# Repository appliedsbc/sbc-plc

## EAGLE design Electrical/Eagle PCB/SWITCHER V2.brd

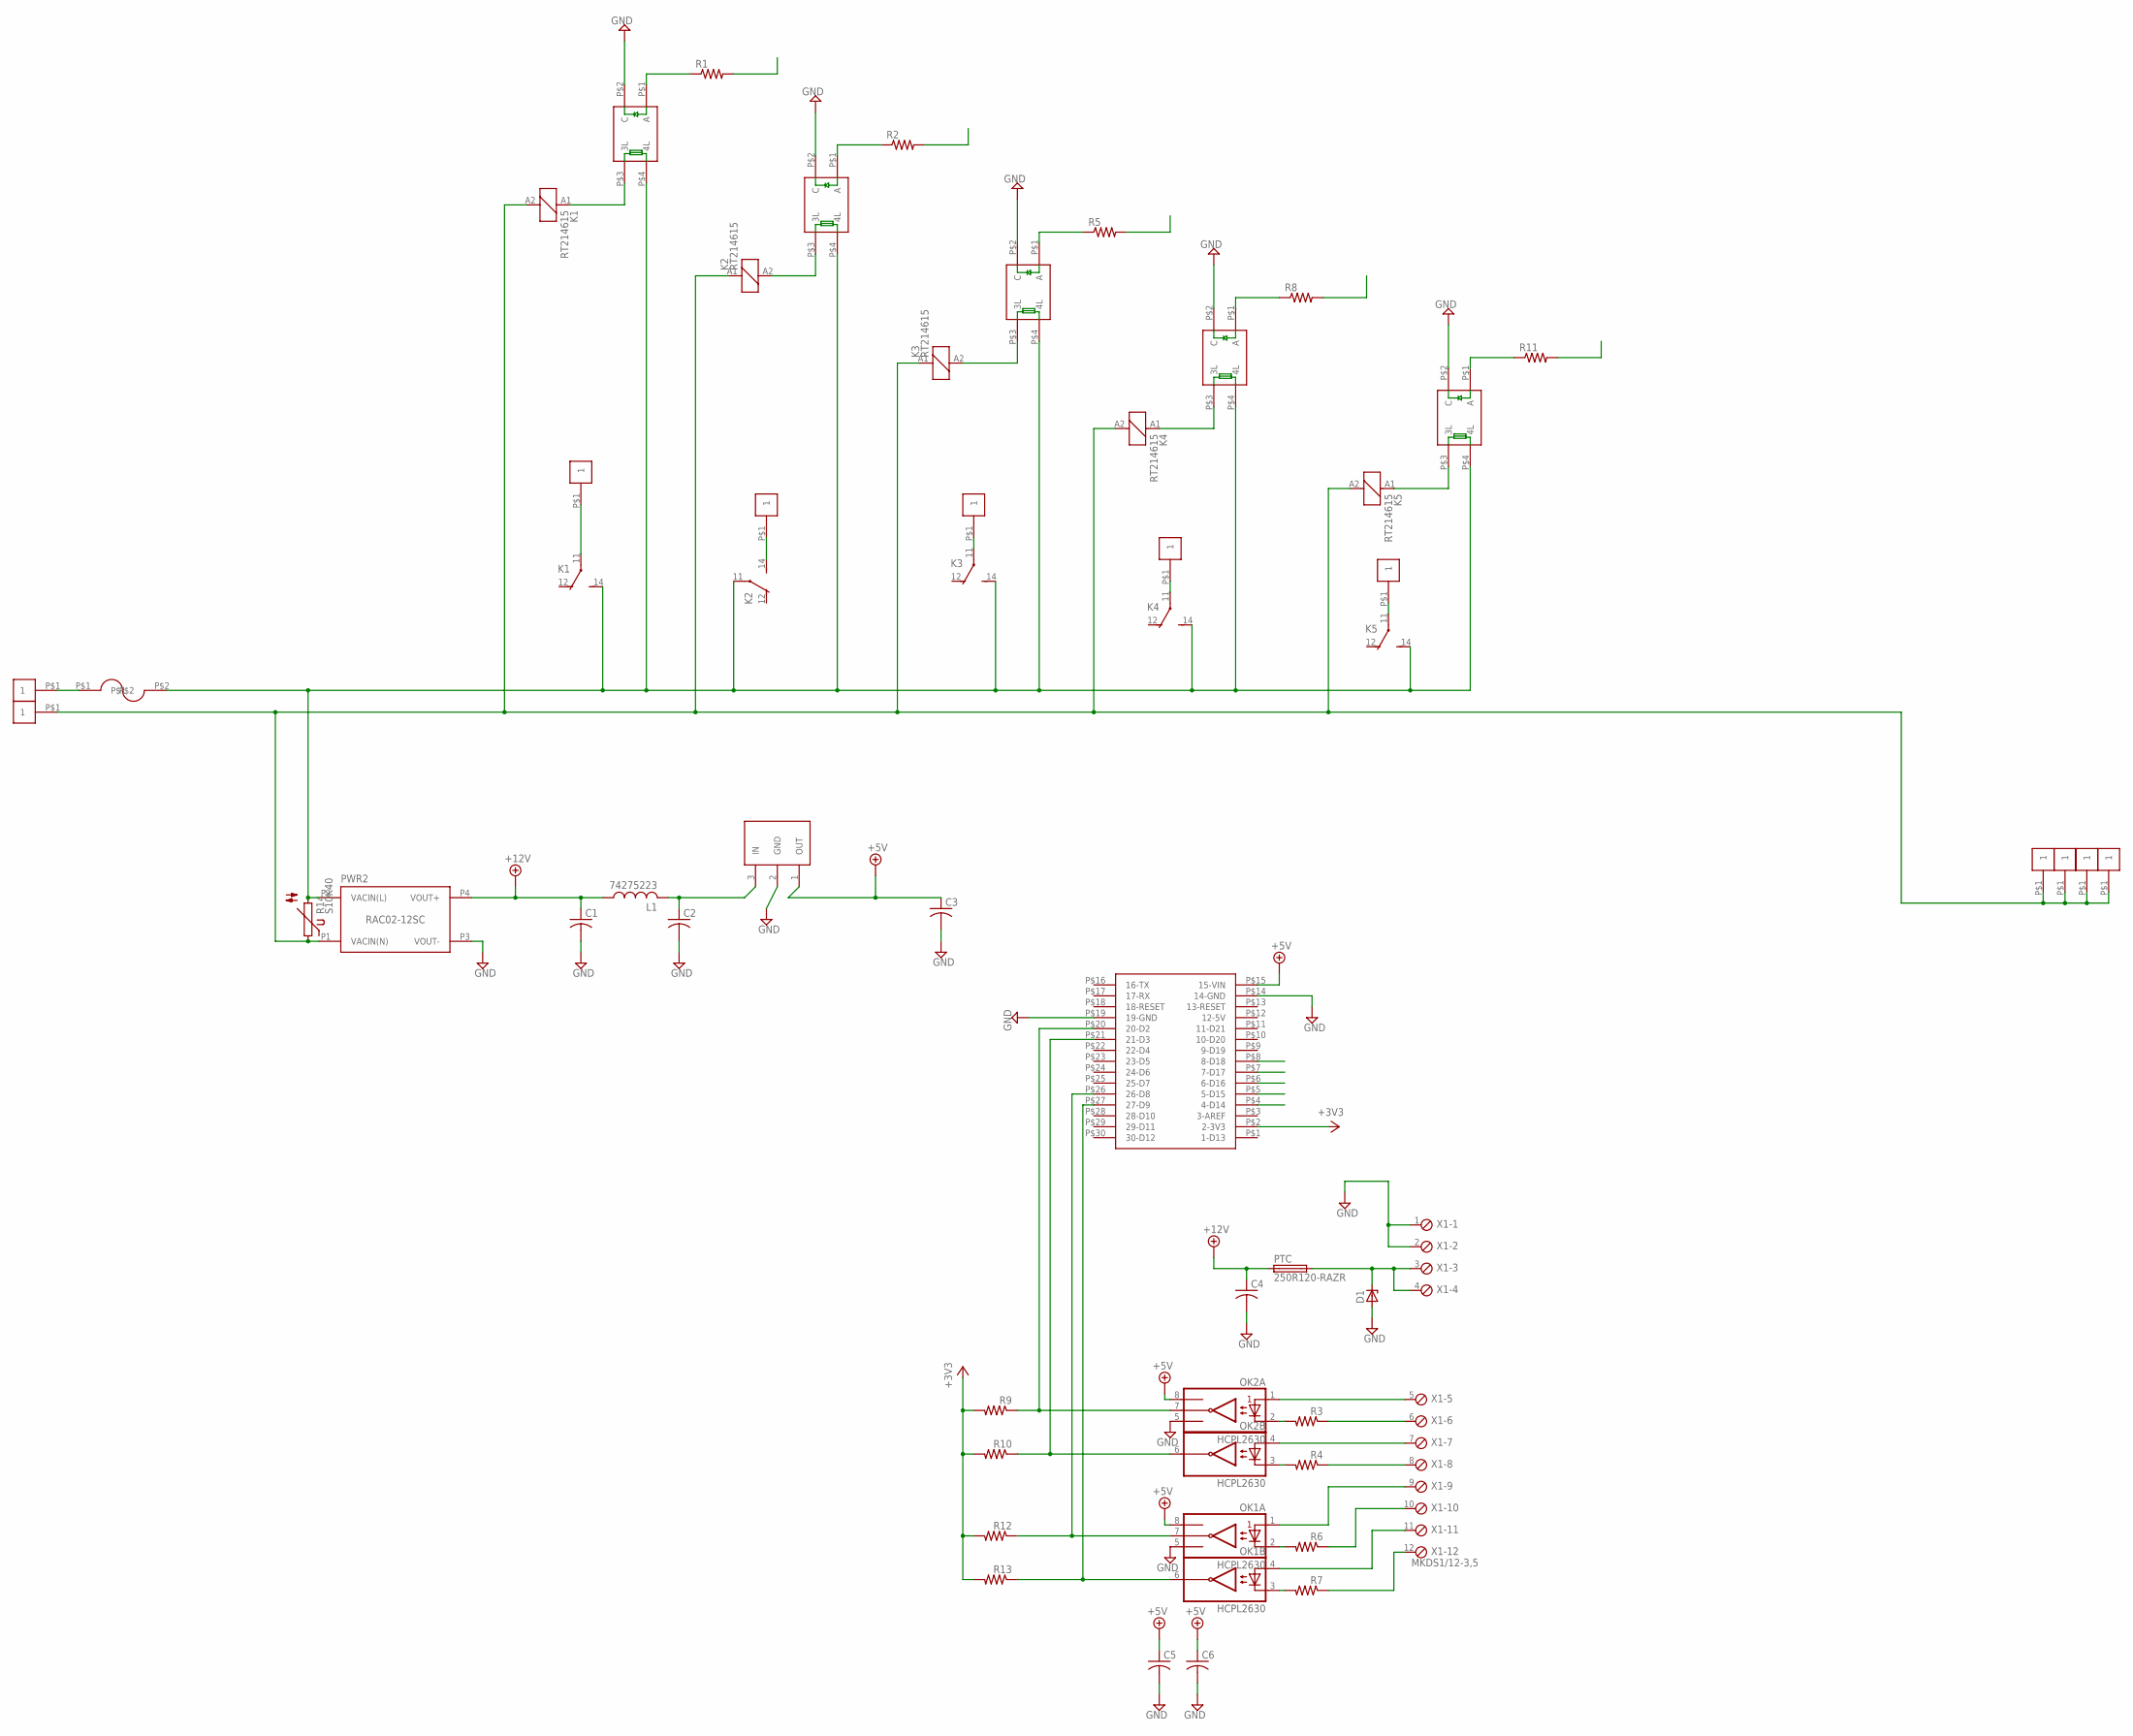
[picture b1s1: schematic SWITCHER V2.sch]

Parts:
C1, C2, C3, C5, C6: C-US025-024X044; C025-024X044
C4: C-US050-025X075; C050-025X075
D1: ZENER-DIODEZD-5; ZDIO-5
K1, K2, K3, K4, K5: RT214615; RT-C/O12A5
L1: 74275223; 6000-XXXX-RC
OK1, OK2: HCPL2630; DIL08
PTC: 250R120-RAZR; TE5
PWR2: RAC02-12SC; LOW_PROFILE_POWER_MODULE
R1, R2, R3, R4, R5, R6, R7, R8, R9, R10, R11, R12, R13: R-US_0204/7; 0204/7
R14: S10K40
U$1, U$4, U$5, U$6, U$7: CPC1393; CPC1393G
U$2, U$11, U$12, U$13, U$14, U$21, U$22, U$25, U$26, U$27, U$28: 089RIVET; KEYSTONE33
U$3: T9-818
U$8: TL750; TO92-OVAL
U$9: ARDUINO-NANO-EVERY
X1: MKDS1/12-3,5; 12POL350

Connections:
+3V3: R9.2, R10.2, R12.2, R13.2, U$9.P$2 (2-3V3)
+5V: C3.1, C5.1, C6.1, OK1.8 (VCC), OK2.8 (VCC), U$8.1 (OUT), U$9.P$15 (15-VIN)
+12V: C1.1, C4.1, L1.1, PTC.1, PWR2.P4 (VOUT+)
BREAKER-L: K1.14 (S), K2.11, K3.14 (S), K4.14 (S), K5.14 (S), PWR2.P2 (VACIN(L)), R14.2, U$1.P$4 (4L), U$3.P$2, U$4.P$4 (4L), U$5.P$4 (4L), U$6.P$4 (4L), U$7.P$4 (4L)
D14: R1.2, U$9.P$4 (4-D14)
D15: R2.2, U$9.P$5 (5-D15)
D16: R11.2, U$9.P$6 (6-D16)
D17: R8.2, U$9.P$7 (7-D17)
D18: R5.2, U$9.P$8 (8-D18)
GND: C1.2, C2.2, C3.2, C4.2, C5.2, C6.2, D1.A, OK1.5 (GND), OK2.5 (GND), PWR2.P3 (VOUT-), U$1.P$2 (C), U$4.P$2 (C), U$5.P$2 (C), U$6.P$2 (C), U$7.P$2 (C), U$8.2 (GND), U$9.P$14 (14-GND), U$9.P$19 (19-GND), X1.1, X1.2
unnamed: U$2.P$1, U$3.P$1
unnamed: C2.1, L1.2, U$8.3 (IN)
unnamed: K2.14 (S), U$25.P$1
unnamed: OK1.3 (C2), R7.2
unnamed: OK2.7 (VO1), R9.1, U$9.P$20 (20-D2)
unnamed: K2.A2 (2), U$4.P$3 (3L)
unnamed: R2.1, U$4.P$1 (A)
unnamed: OK2.6 (VO2), R10.1, U$9.P$21 (21-D3)
unnamed: K1.11, U$21.P$1
unnamed: OK2.1 (A1), X1.5
unnamed: K1.A1 (1), U$1.P$3 (3L)
unnamed: R1.1, U$1.P$1 (A)
unnamed: K5.11, U$28.P$1
unnamed: R3.1, X1.6
unnamed: K4.11, U$27.P$1
unnamed: OK1.2 (C1), R6.2
unnamed: K3.11, U$26.P$1
unnamed: OK2.3 (C2), R4.2
unnamed: OK2.2 (C1), R3.2
unnamed: OK2.4 (A2), X1.7
unnamed: K3.A2 (2), U$5.P$3 (3L)
unnamed: R5.1, U$5.P$1 (A)
unnamed: R4.1, X1.8
unnamed: OK1.7 (VO1), R12.1, U$9.P$26 (26-D8)
unnamed: D1.C, PTC.2, X1.3, X1.4
unnamed: OK1.6 (VO2), R13.1, U$9.P$27 (27-D9)
unnamed: OK1.1 (A1), X1.9
unnamed: K4.A1 (1), U$6.P$3 (3L)
unnamed: R8.1, U$6.P$1 (A)
unnamed: R6.1, X1.10
unnamed: OK1.4 (A2), X1.11
unnamed: R7.1, X1.12
unnamed: K5.A1 (1), U$7.P$3 (3L)
unnamed: R11.1, U$7.P$1 (A)
unnamed: K1.A2 (2), K2.A1 (1), K3.A1 (1), K4.A2 (2), K5.A2 (2), PWR2.P1 (VACIN(N)), R14.1, U$11.P$1, U$12.P$1, U$13.P$1, U$14.P$1, U$22.P$1

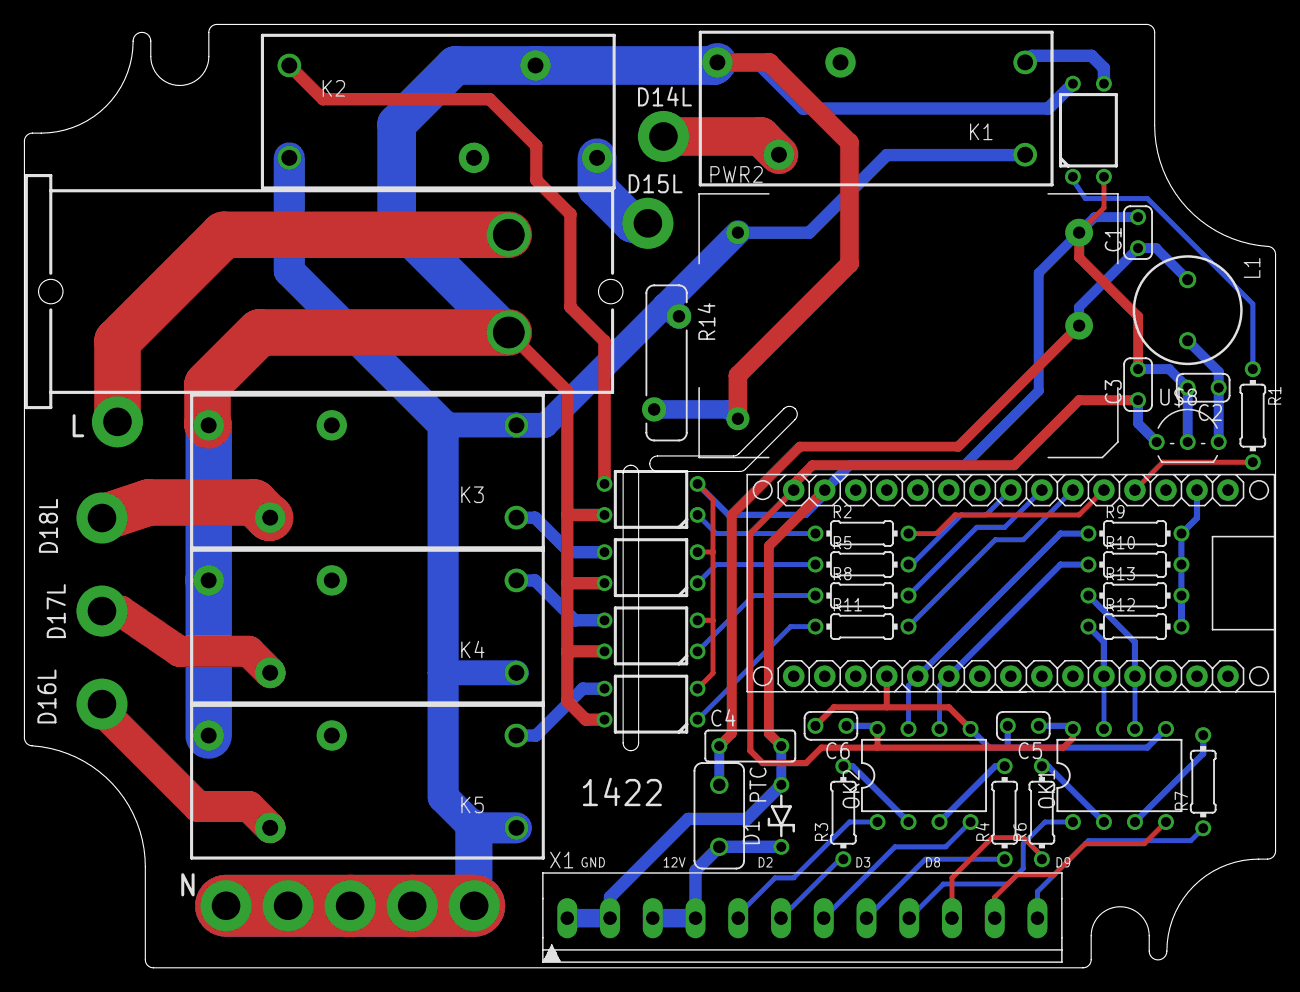
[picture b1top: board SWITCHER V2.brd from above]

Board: 2 copper layers, 102.4 x 77.2 mm, 51 parts (0 on the bottom side), 45 nets.

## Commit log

2022-05-20 added images
